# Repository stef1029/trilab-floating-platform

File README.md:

# Floating Platform Orienting System — Project Specification

A head-fixed behavioural platform for studying sensory-guided spatial orienting in mice.

> **Status:** Design specification and prototyping. This readme defines the scientific intent,
> design principles, and requirements for the system.

---

## 1. Background and Motivation

### 1.1 The problem of spatial orienting

Orienting towards environmental stimuli is a fundamental behaviour conserved across the
animal kingdom: an animal turns its eyes, head, and body to bring a salient stimulus into
its sensory and motor focus. Although subjectively effortless, orienting requires the
nervous system to solve several hard computational problems at once:

- **Coordinate-frame transformation.** Different senses encode space in incompatible
  reference frames (vision in retinotopic coordinates, hearing in head-centred coordinates,
  touch in body-centred coordinates) yet the motor system needs a single unified target.
- **Sensorimotor transformation.** A spatial estimate must be converted into a coordinated
  motor command spanning effectors with very different dynamics (fast, low-range eyes; slower,
  wider-range head; slow, widest-range body).
- **Target selection.** When multiple stimuli compete, the system must commit to a single
  target, the body cannot turn two ways at once.

### 1.2 The superior colliculus (SC)

The SC is an evolutionarily ancient midbrain hub (circuits >500 My old) that sits at the
centre of this problem. It receives topographically aligned, convergent input from
essentially every sensory modality and contains a motor map from which electrical or
optogenetic stimulation reliably evokes orienting movements toward the corresponding
location. Beyond driving movement, accumulating evidence implicates the SC in **spatial
priority / attention**: it is thought to maintain a *priority map* that integrates bottom-up
salience with top-down task relevance, gating both descending orienting commands and
ascending thalamo-cortical signals.

### 1.3 The methodological gap this system addresses

Mouse genetics (Cre-driver lines, optogenetics, optotagging, calcium imaging, two-photon,
high-density electrophysiology) make the mouse SC uniquely tractable for circuit dissection.
But existing mouse paradigms force a trade-off:

| Approach | Strength | Weakness |
|---|---|---|
| **Head-fixed** (2-photon, Neuropixels, VR) | Maximal experimental control, high trial counts, recording/manipulation access | Sacrifices the natural whole-body orienting repertoire; reporting movements are abstract (e.g. licking, wheel turns) |
| **Freely moving** (escape, prey capture, social orienting) | Full natural movement repertoire, ethological validity | Low trial counts, behavioural adaptation/disengagement, hard to standardise and track, limited tool access |

**Design thesis:** a head-fixed preparation that *preserves rotational orienting kinematics*
by mounting the animal on a low-friction, air-floated platform can recover much of the
ethological character of orienting while retaining the recording/manipulation access and
trial structure of head fixation. This is the niche the floating platform system is intended
to fill. Closely related precedents exist in the ferret sound-localisation literature
(approach-to-target paradigms) and in air-lifted platform preparations for rodents; the
novelty here is combining controlled rotational orienting with head fixation and modern
mouse circuit tools.

> **Terminology.** This document follows the *orienting* vs *localisation* distinction
> (Nodal et al., 2008). *Orienting* is the unconditioned, continuously-varying movement of
> eyes/head/body toward a stimulus. *Localisation* (approach-to-target) is the conditioned
> report of perceived location via a discrete choice. This platform is designed to capture
> the **orienting movement itself as a continuous dependent variable**, not merely the
> categorical choice.

---

## 2. Scientific Design Principles

These principles flow directly from the science above and should govern every engineering
trade-off.

1. **Preserve orienting kinematics.** The animal must be able to produce naturalistic
   rotational orienting movements. The platform's mechanics (mass, inertia, friction) must be
   matched to mouse motor capability so that orienting is *natural and low-effort*, not a
   novel motor skill the animal must laboriously acquire. **Movement accessibility is a
   first-order scientific requirement, not an engineering nicety.**

2. **Multiple spatial targets.** Move beyond binary left/right. The animal must be able to
   orient toward stimuli distributed around it, so the system can probe the full spatial map
   of the SC.

3. **Movement as the primary readout.** The dependent variable is the *trajectory* of the
   orienting movement (bearing, latency, amplitude, velocity profile), not just an endpoint.
   This demands continuous, high-resolution measurement of platform orientation.

4. **Multimodal cueing.** Support visual and auditory cues (and ideally the means to add
   somatosensory), so cue modality and coordinate frame can be dissociated — central to
   testing how heterogeneous sensory inputs are transformed into a common motor currency.

5. **Recording- and manipulation-ready from day one.** The system exists to support
   electrophysiology, optogenetics/chemogenetics, and imaging. Compatibility with these tools
   — physical access, electromagnetic compatibility, and above all **temporal
   synchronisation** — must be designed in, not retrofitted.

6. **Trial structure and throughput.** Standardised, self-paced trials with clean
   trial/inter-trial separation, at counts sufficient for statistically powerful,
   circuit-level conclusions.

7. **Respect the animal.** Welfare-conscious head fixation and handling; training timelines
   that are realistic for a cohort within a project's lifetime.

---

## 3. Requirements

### 3.1 Functional requirements (behaviour)

- **F1 — Rotational freedom.** The mouse, while head-fixed, can rotate the floating platform
  beneath it to produce orienting movements through its full natural range, with friction low
  enough that movement is effortless.
- **F2 — Constrained degrees of freedom.** Platform motion is constrained to the behaviourally
  meaningful axes (rotation, translation).
- **F3 — Multi-target cueing.** Present discrete spatial cues at ≥4 (target: 6) locations
  distributed around the animal, with unambiguous angular separation.
- **F4 — Multimodal cues.** Independently addressable **visual** (per-location LED) and
  **auditory** (per-location or spatialised speaker) cue channels; spare capacity for a third
  modality.
- **F5 — Reward delivery.** Precise, low-latency liquid reward (calibrated µL volumes) at each
  target location, with reliable consumption detection.
- **F6 — Response detection.** Detect the animal's chosen orientation/target reliably and with
  low latency (event timing to ≤1 ms), with no false positives/negatives from the sensing
  modality.
- **F7 — Self-paced trial initiation.** A clear, animal-driven readiness/initiation event that
  separates trials from inter-trial intervals and standardises starting conditions.
- **F8 — Configurable protocol.** Cue duration, cue modality, target set, reward contingency,
  timeout, and inter-trial interval all configurable per session and per training phase,
  without code surgery.

### 3.2 Measurement requirements

- **M1 — Continuous orientation tracking.** Platform angular position sampled continuously at
  high temporal resolution (target ≥100 Hz, ideally faster) and angular precision sufficient
  to reconstruct full orienting trajectories — not just endpoints.
- **M2 — Absolute reference where possible.** Orientation measurement should resolve absolute
  bearing (not only relative drift), or provide robust per-trial re-zeroing against a known
  reference event.
- **M3 — Low-light operation.** Behaviour runs under controlled, mouse-appropriate lighting
  (e.g. long-wavelength / IR illumination); the tracking method must work under these
  conditions without motion blur or illumination that interferes with the visual task.
- **M4 — Video record.** Synchronised overhead and/or side video for behavioural scoring and
  markerless pose estimation.

### 3.3 Technical / systems requirements

- **T1 — Unified timing backbone (highest priority).** A single timing authority records all
  event streams — cue onset/offset, reward, response, orientation samples, video frame
  triggers, and external equipment (ephys/laser) sync — on one clock with **≤1 ms** alignment
  across streams. *Lack of hardware-level synchronisation is the single most likely failure
  mode of a behavioural-neuroscience rig and must be solved at the architecture level.*
- **T2 — Drop detection on every stream.** Every data stream (serial messages, camera frames)
  must carry sequence IDs / frame counters so that dropped samples are detectable and
  correctable post-hoc, never silently misaligning data.
- **T3 — External-equipment sync.** Generate and/or record TTL sync with electrophysiology
  acquisition and optogenetic laser control, so neural data and behaviour share a common time
  base.
- **T4 — Electromagnetic compatibility.** Construction and grounding compatible with
  electrophysiology (shielding / Faraday behaviour; low 50 Hz pickup; no conductive paths to
  electrodes).
- **T5 — Deterministic real-time control.** Time-critical operations (reward, response
  sensing, cue timing) handled with deterministic latency; high-level trial logic and logging
  separated from real-time control.
- **T6 — Automated session lifecycle.** One-command session start that configures and launches
  all subsystems (control, acquisition, cameras) in the correct order; automated logging with
  crash recovery.
- **T7 — Standardised, analysis-ready data.** Output to a documented, standard format (e.g.
  NWB) with an accompanying pipeline from raw streams → synchronised, trial-segmented dataset
  → quality-control metrics → figures, minimising manual steps.
- **T8 — Maintainability & reproducibility.** Modular, serviceable hardware (swappable
  per-target modules); liquid-tolerant construction; documented build so additional rigs can
  be replicated by the lab.
- **T9 — Session endurance.** Sustain a full behavioural session (target: continuous operation
  for multi-hour daily use) without power, thermal, or buffer constraints forcing early
  termination.

### 3.4 Non-functional requirements

- **N1 — Welfare.** Graduated head-fixation habituation; comfortable, low-stress fixation;
  bounded session durations.
- **N2 — Trainability.** A naïve mouse should reach criterion performance within a timeframe
  practical for a 10–12 animal cohort. *(Because mechanical accessibility (F1) directly
  governs trainability, the platform's inertia/friction budget should be validated against
  mouse motor output early.)*
- **N3 — Cost & scalability.** Favour designs that allow multiple rigs to run in parallel on
  shared infrastructure without duplicating the most expensive components.

---

## 4. Proposed System Description

A concrete architecture that satisfies the requirements above. Subsystems are described by
*function and constraints*; exact components are deliberately left open where the science does
not yet dictate them.

### 4.1 Mechanical core — the floating platform

- A lightweight, rigid platform (e.g. machined low-density foam) suspended on a **cushion of
  air** above a perforated, regulated air table, giving near-frictionless motion.
- Air supply regulated to lift the loaded platform (platform + onboard electronics) at a
  stable hover height with negligible residual friction.
- **Motion constrained** to the behaviourally relevant axes — primarily rotation (and
  optionally controlled fore/aft translation) — using physical guides, while blocking
  lateral/vertical excursions.
- **Inertia budget:** the rotational moment of inertia of the loaded platform must be small
  relative to the torque a mouse can comfortably generate. This is the central mechanical
  constraint and should be minimised (light platform, minimal onboard mass, balanced about the
  rotation axis) and validated empirically against mouse motor capability before committing.
- A low surrounding wall prevents falls without restricting movement and provides a mounting
  surface for cue/reward modules and/or tracking references.

### 4.2 Head-fixation assembly

- Standard, welfare-conscious head-bar fixation (off-the-shelf optomechanics) positioning the
  animal centrally over the platform's rotation axis, leaving the body free to drive platform
  rotation.
- Fixation height and posture chosen so that orienting is produced by natural weight-shift /
  stepping, not an artificial motor strategy.

### 4.3 Target / cue / reward modules

- A ring of **modular, independently serviceable target stations** at fixed angular intervals
  (target: 6 at 60°, minimum 4 at 90°).
- Each station integrates: a **visual cue** (high-brightness LED), an **auditory cue**
  (speaker), a **liquid reward** spout (solenoid/pinch-valve, gravity- or pump-fed, calibrated
  volume), and a **response/consumption sensor** (e.g. IR beam-break — preferred over
  capacitive sensing for reliability).
- Modularity allows a faulty station to be swapped without disturbing the rig and supports
  rapid prototyping of new configurations.

### 4.4 Orientation tracking

Continuous platform-orientation measurement is mandatory (M1–M3). The architecture should
support — and ideally fuse — complementary methods, chosen for robustness under low-light
operation:

- An **inertial measurement unit (IMU)** mounted on the platform for high-rate relative
  orientation, re-zeroed each trial against a known reference event (giving high within-trial
  accuracy).
- And/or an **absolute optical reference** (e.g. fiducial markers read by a camera, or an
  optical/magnetic angular encoder on the rotation axis) for absolute bearing and drift
  correction — noting that any camera-based method must tolerate the IR/low-light regime and
  platform motion without blur.
- **Markerless pose estimation** (e.g. DeepLabCut) on synchronised video as an independent
  cross-check and for body/limb kinematics.

### 4.5 Control and acquisition architecture

The defining architectural commitment: **separate real-time control from timing/logging.**

- **Real-time controller** (microcontroller): owns deterministic, time-critical hardware
  control — cue timing, reward actuation, response sensing — and nothing else. Prefer a
  microcontroller with **native USB** (low, deterministic serial latency) over legacy
  serial-to-USB bridges.
- **Independent acquisition / timing backbone (DAQ):** a dedicated device that does nothing
  but sample *all* digital/analogue lines (cue states, sensor states, reward signals) plus
  external sync (camera frame TTLs, ephys clock, laser control) at high rate (target ≥1 kHz,
  ideally ≥10 kHz) onto **one clock**. Every message carries a sequence ID (T2).
- **Host computer:** runs high-level trial logic / state machine, configuration, multi-rig
  orchestration, real-time performance metrics, and all file writing (offloading I/O from
  embedded devices). Launches the whole session with one command (T6).
- **Cameras:** programmatically controlled (not via a GUI), emitting a TTL per frame into the
  DAQ and saving hardware frame IDs, so dropped frames are detectable and video aligns to the
  behavioural timeline to the frame.

This separation is what delivers T1–T3: a single timestamped record into which neural,
video, and behavioural events all map without clock drift.

### 4.6 Software, data, and analysis pipeline

- **Configurable protocol engine** encoding training phases and trial parameters via
  configuration, not code edits (F8).
- **Standardised output** (NWB or equivalent) bundling synchronised event streams, orientation
  traces, video references, and trial metadata, with crash-recovery/backup.
- **Automated post-processing**: parse DAQ logs → reconstruct trials → align video via frame
  IDs → run pose estimation → emit a trial-segmented dataset plus QC metrics, with minimal
  manual intervention.
- **Cohort/session data model** giving programmatic access (query by animal, date, completion
  status) so analyses run over whole cohorts in little code.

### 4.7 Behavioural protocol (intended)

1. **Initiation.** The animal produces a defined, self-paced readiness event that standardises
   the starting orientation and separates trials from inter-trial intervals (F7). The
   initiation requirement must be designed to genuinely standardise starting conditions
   (minimising preparatory movement before cue onset).
2. **Cue.** One target is cued (visual and/or auditory), with configurable duration.
3. **Orienting response.** The animal rotates the platform to bring the cued target into
   reach; the full trajectory is recorded.
4. **Outcome.** Correct orientation → immediate calibrated reward. Incorrect → brief timeout,
   no reward.
5. **Reset.** Return to initiation for the next self-paced trial.

---

## 5. Key Open Design Questions / Risks

Flagged up front because they drive the riskiest decisions:

- **Mechanical accessibility vs. control (F1/N2).** Can the inertia/friction budget be made
  low enough that a head-fixed mouse produces natural orienting rotations *and* learns the task
  in a cohort-feasible timeframe? This is the make-or-break biological-mechanical question and
  should be de-risked first with simple motor-capability tests.
- **Tracking under low light (M1–M3).** Reconciling absolute, blur-free, high-rate orientation
  measurement with the dim/IR lighting the visual task requires. IMU + absolute-encoder fusion
  is the conservative hedge.
- **Initiation standardisation (F7).** Defining an initiation behaviour that truly fixes
  starting orientation without permitting covert preparatory movement.
- **Synchronisation throughput (T1).** Achieving the target sample/frame rates without
  message loss; choice of controller and DAQ should leave headroom above the minimum.

---

## 6. Key References

Foundational citations that justify the design intent.

**Superior colliculus, orienting, and spatial priority**
- May, P. J. (2006). The mammalian superior colliculus: laminar structure and connections.
  *Prog. Brain Res.* 151. — SC anatomy and laminar organisation.
- Sparks, D. L. & Mays, L. E. (1990). Signal transformations required for the generation of
  saccadic eye movements. *Annu. Rev. Neurosci.* 13. — SC sensorimotor transformation.
- Fecteau, J. H. & Munoz, D. P. (2006). Salience, relevance, and firing: a priority map for
  target selection. *Trends Cogn. Sci.* 10. — priority-map concept.
- Krauzlis, R. J., Lovejoy, L. P. & Zénon, A. (2013). Superior colliculus and visual spatial
  attention. *Annu. Rev. Neurosci.* 36. — SC role in attention beyond movement.
- Knudsen, E. I. (2018). Neural circuits that mediate selective attention: a comparative
  perspective. *Trends Neurosci.* 41. — gating and selective attention.
- de Malmazet, D. & Tripodi, M. (2023). Collicular circuits supporting the perceptual, motor
  and cognitive demands of ethological environments. *Curr. Opin. Neurobiol.* 82.
- Masullo, L. et al. (2019). Genetically defined functional modules for spatial orienting in
  the mouse superior colliculus. *Curr. Biol.* 29. — Pitx2+ SC output neurons; target
  population for manipulation.

**Behavioural paradigms and precedents**
- Parsons, C. H., Lanyon, R. G., Schnupp, J. W. H. & King, A. J. (1999). *J. Neurophysiol.* 82.
  — ferret sound-localisation / approach-to-target precedent.
- Nodal, F. R. et al. (2008). Sound localisation behaviour in ferrets: acoustic orientation vs
  approach-to-target. *Neuroscience* 154. — the orienting vs localisation distinction.
- Robbins, T. W. (2002). The 5-choice serial reaction time task. *Psychopharmacology* 163. —
  multi-choice spatial reporting paradigm.
- Guo, Z. V. et al. (2014). Procedures for behavioral experiments in head-fixed mice. *PLoS
  ONE* 9. — head-fixed behavioural standards.
- Kislin, M. et al. (2014). Flat-floored air-lifted platform: combining behaviour with
  microscopy/electrophysiology on awake freely moving rodents. *JoVE*. — air-lifted platform
  precedent.
- Angelaki, D. et al. (2025). A brain-wide map of neural activity during complex behaviour.
  *Nature* 645. — mice performing complex standardised tasks.

**Tools and infrastructure**
- Denman, D. J. et al. (2017). Chromatic pathways in the mouse dLGN. *J. Neurosci.* 37. —
  basis for long-wavelength lighting choices for mouse vision.
- Mathis, A. et al. (2018). DeepLabCut: markerless pose estimation. *Nat. Neurosci.* 21.
- Rübel, O. et al. (2022). The Neurodata Without Borders ecosystem. *eLife* 11. — standardised
  data format.

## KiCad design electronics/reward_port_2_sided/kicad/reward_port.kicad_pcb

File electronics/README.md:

# Electronics

KiCad projects, schematics, PCB layouts, BOMs, and fabrication outputs.

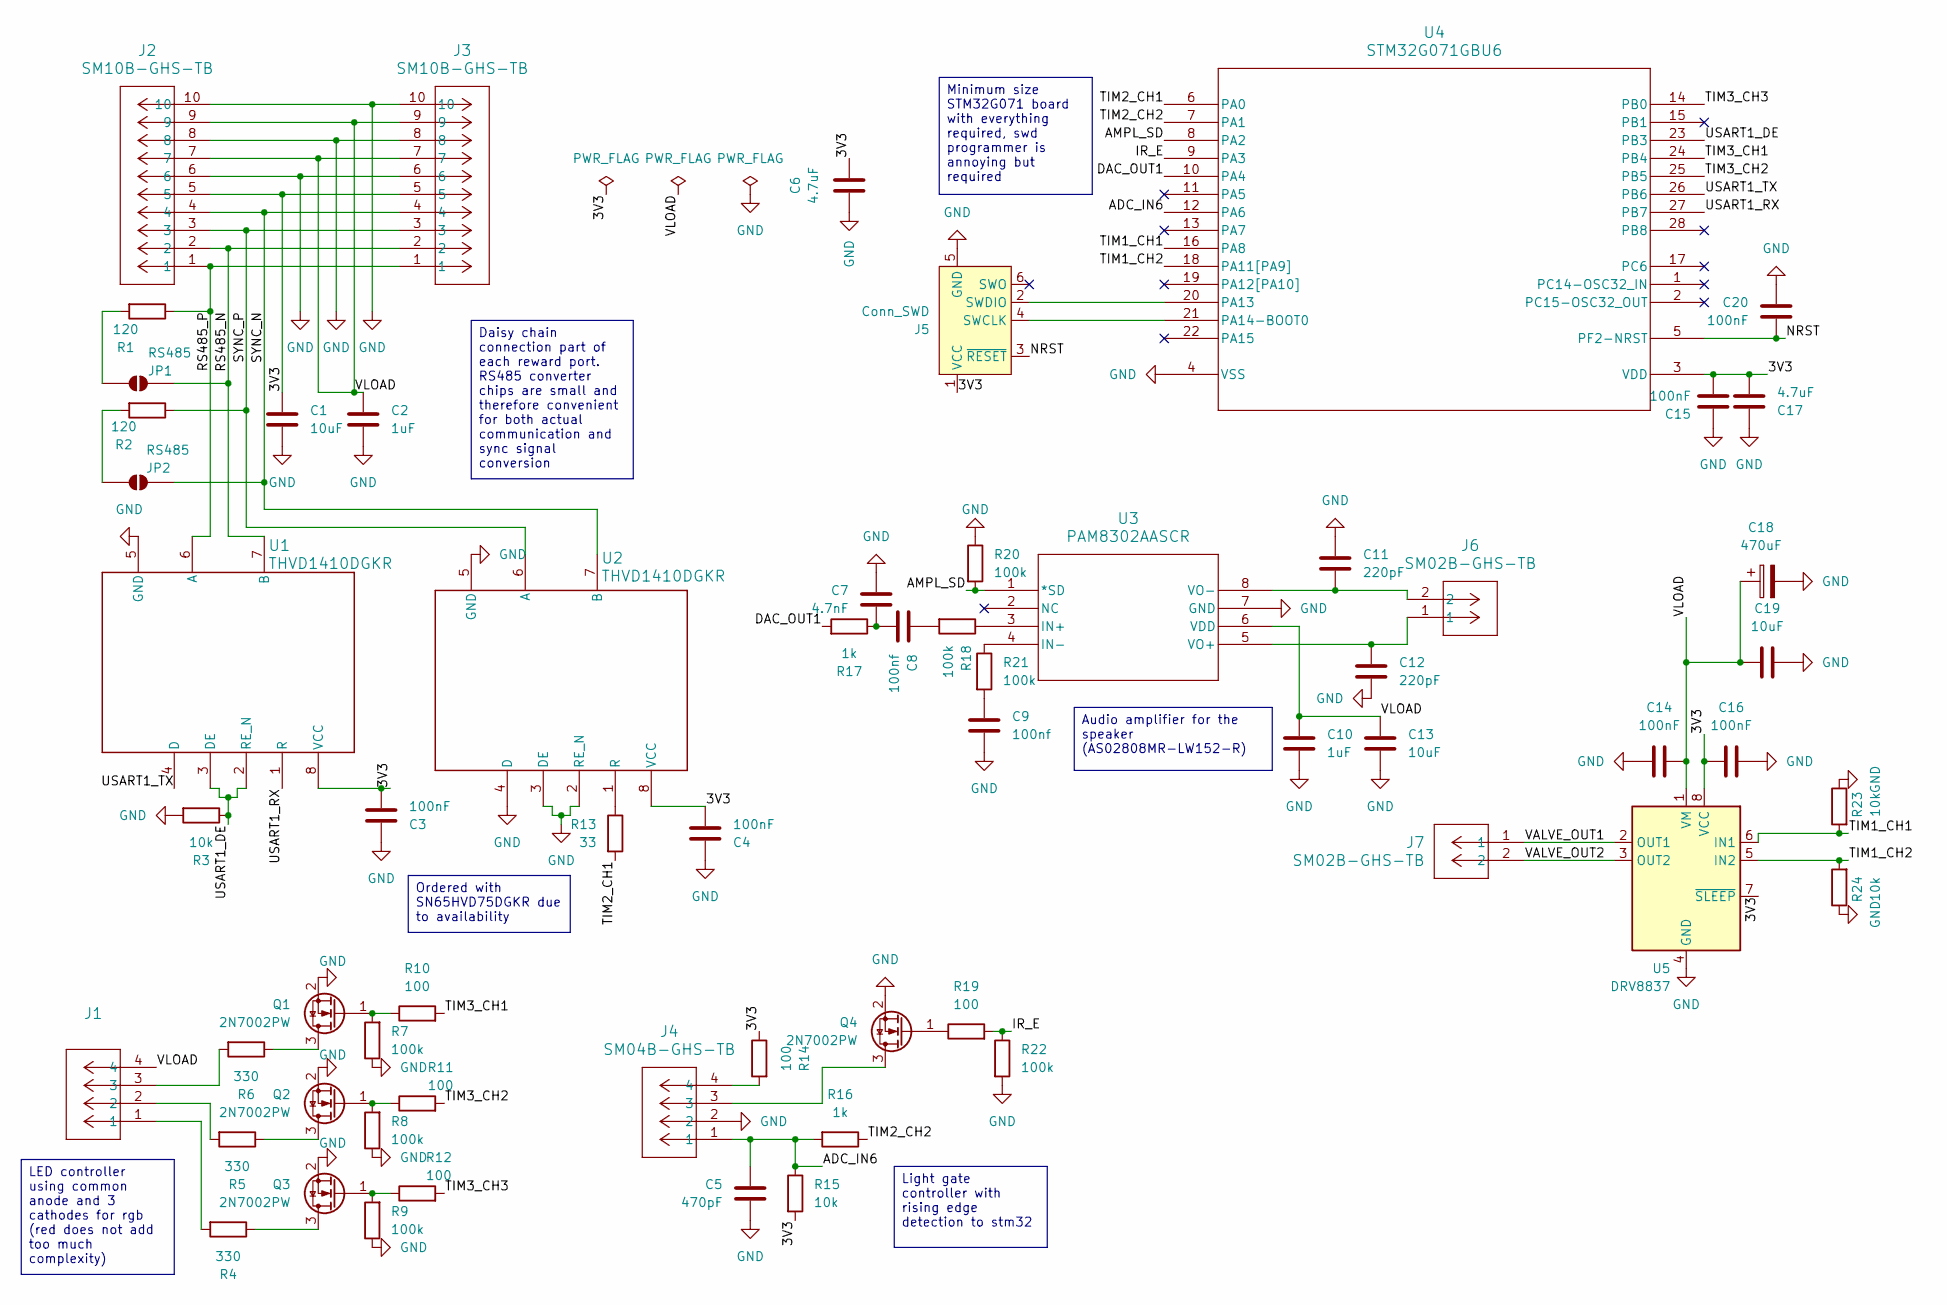
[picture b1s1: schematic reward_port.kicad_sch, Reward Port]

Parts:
C1, C19: 10uF; C_0603_1608Metric
C2, C10: 1uF; C_0402_1005Metric
C3, C4, C14, C15, C16, C20: 100nF; C_0402_1005Metric
C5: 470pF; C_0402_1005Metric
C6, C17: 4.7uF; C_0603_1608Metric
C7: 4.7nF; C_0402_1005Metric
C8, C9: 100nf; C_0402_1005Metric
C11, C12: 220pF; C_0402_1005Metric
C13: 10uF; C_0805_2012Metric
C18: 470uF; CP_EIA-7343-43_Kemet-X
J1, J4: SM04B-GHS-TB; JST_GH_SM04B-GHS-TB_1x04-1MP_P1.25mm_Horizontal
J2, J3: SM10B-GHS-TB; JST_PH_S10B-PH-SM4-TB_1x10-1MP_P2.00mm_Horizontal
J5: Conn_SWD; Tag-Connect_TC2030-IDC-NL_2x03_P1.27mm_Vertical
J6, J7: SM02B-GHS-TB; JST_GH_SM02B-GHS-TB_1x02-1MP_P1.25mm_Horizontal
JP1, JP2: RS485; SolderJumper-2_P1.3mm_Open_RoundedPad1.0x1.5mm
Q1, Q2, Q3, Q4: 2N7002PW; SOT-323_SC-70
R1, R2: 120; R_0603_1608Metric
R3, R15, R23, R24: 10k; R_0402_1005Metric
R4, R5, R6: 330; R_0402_1005Metric
R7, R8, R9, R18, R20, R21, R22: 100k; R_0402_1005Metric
R10, R11, R12, R19: 100; R_0402_1005Metric
R13: 33; R_0402_1005Metric
R14: 100; R_0603_1608Metric
R16, R17: 1k; R_0402_1005Metric
U1, U2: THVD1410DGKR; VSSOP-8_3x3mm_P0.65mm
U3: PAM8302AASCR; PAM8302AASCR_DIO
U4: STM32G071GBU6; QFN-28_4x4mm_P0.5mm
U5: DRV8837; WSON-8-1EP_2x2mm_P0.5mm_EP0.9x1.6mm

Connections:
/3V3: C1.1, C3.1, C4.1, C6.1, C15.2, C16.1, C17.1, J2.5, J3.5, J5.1 (VCC), R14.1, R15.2, U1.8 (VCC), U2.8 (VCC), U4.3 (VDD), U5.7 (~SLEEP), U5.8 (VCC)
/ADC_IN6: C5.2, J4.1, R15.1, R16.2, U4.12 (PA6)
/AMPL_SD: R20.2, U3.1 (*SD), U4.8 (PA2)
/DAC_OUT1: R17.2, U4.10 (PA4)
/IR_E: R19.2, R22.1, U4.9 (PA3)
/NRST: C20.1, J5.3 (~RESET), U4.5 (PF2-NRST)
/RS485_N: J2.2, J3.2, JP1.2 (B), U1.7 (B)
/RS485_P: J2.1, J3.1, R1.1, U1.6 (A)
/SYNC_N: J2.4, J3.4, JP2.2 (B), U2.7 (B)
/SYNC_P: J2.3, J3.3, R2.1, U2.6 (A)
/TIM1_CH1: R23.2, U4.16 (PA8), U5.6 (IN1)
/TIM1_CH2: R24.2, U4.18 (PA11[PA9]), U5.5 (IN2)
/TIM2_CH1: R13.2, U4.6 (PA0)
/TIM2_CH2: R16.1, U4.7 (PA1)
/TIM3_CH1: R10.2, U4.24 (PB4)
/TIM3_CH2: R11.2, U4.25 (PB5)
/TIM3_CH3: R12.2, U4.14 (PB0)
/USART1_DE: R3.1, U1.2 (RE_N), U1.3 (DE), U4.23 (PB3)
/USART1_RX: U1.1 (R), U4.27 (PB7)
/USART1_TX: U1.4 (D), U4.26 (PB6)
/VALVE_OUT1: J7.1, U5.2 (OUT1)
/VALVE_OUT2: J7.2, U5.3 (OUT2)
/VLOAD: C2.1, C10.1, C13.1, C14.1, C18.1, C19.1, J1.4, J2.7, J2.9, J3.7, J3.9, U3.6 (VDD), U5.1 (VM)
GND: C1.2, C2.2, C3.2, C4.2, C5.1, C6.2, C7.1, C9.2, C10.2, C11.1, C12.1, C13.2, C14.2, C15.1, C16.2, C17.2, C18.2, C19.2, C20.2, J2.6, J2.8, J2.10, J3.6, J3.8, J3.10, J4.2, J5.5 (GND), Q1.2 (S), Q2.2 (S), Q3.2 (S), Q4.2 (S), R3.2, R7.1, R8.1, R9.1, R20.1, R22.2, R23.1, R24.1, U1.5 (GND), U2.2 (RE_N), U2.3 (DE), U2.4 (D), U2.5 (GND), U3.7 (GND), U4.4 (VSS), U5.4 (GND), U5.9 (GND)
unnamed: C7.2, C8.2, R17.1
unnamed: C8.1, R18.2
unnamed: C9.1, R21.2
unnamed: J1.1, R4.2
unnamed: J1.2, R5.2
unnamed: J1.3, R6.2
unnamed: J4.4, R14.2
unnamed: J5.4 (SWCLK), U4.21 (PA14-BOOT0)
unnamed: J5.2 (SWDIO), U4.20 (PA13)
unnamed: JP1.1 (A), R1.2
unnamed: JP2.1 (A), R2.2
unnamed: Q1.3 (D), R6.1
unnamed: Q1.1 (G), R7.2, R10.1
unnamed: Q2.3 (D), R5.1
unnamed: Q2.1 (G), R8.2, R11.1
unnamed: Q3.3 (D), R4.1
unnamed: Q3.1 (G), R9.2, R12.1
unnamed: J4.3, Q4.3 (D)
unnamed: Q4.1 (G), R19.1
unnamed: R13.1, U2.1 (R)
unnamed: R18.1, U3.3 (IN+)
unnamed: R21.1, U3.4 (IN-)
unnamed: C12.2, J6.1, U3.5 (VO+)
unnamed: C11.2, J6.2, U3.8 (VO-)

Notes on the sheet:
Audio amplifier for the speaker (AS02808MR-LW152-R)
Light gate controller with rising edge detection to stm32
Daisy chain connection part of each reward port. RS485 converter chips are small and therefore convenient for both actual communication and sync signal conversion
Minimum size STM32G071 board with everything required, swd programmer is annoying but required
Ordered with SN65HVD75DGKR due to availability
LED controller using common anode and 3 cathodes for rgb (red does not add too much complexity)

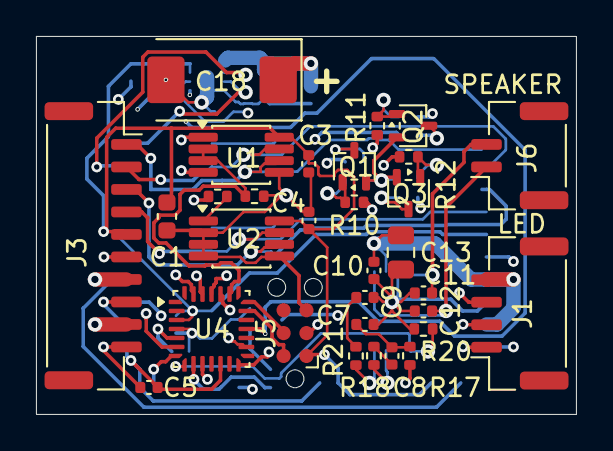
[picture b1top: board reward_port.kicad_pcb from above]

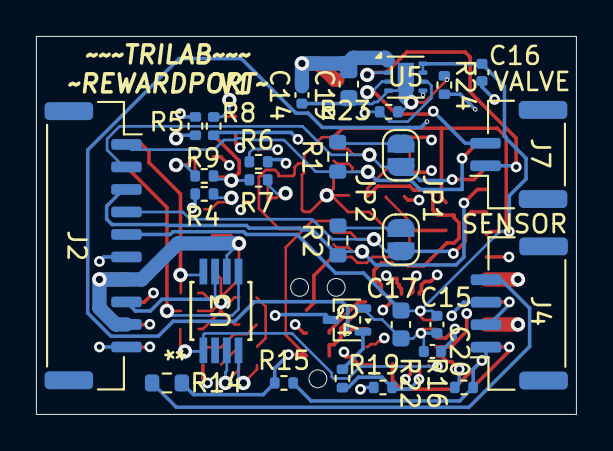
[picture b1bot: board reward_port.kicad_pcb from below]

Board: 4 copper layers, 30.0 x 21.0 mm, 60 parts (29 on the bottom side), 48 nets.

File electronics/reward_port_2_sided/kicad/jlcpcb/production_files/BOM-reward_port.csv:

Comment,Designator,Footprint,LCSC,Quantity
100,R14,R_0603_1608Metric,C22775,1
100,"R10,R11,R12,R19",R_0402_1005Metric,C25076,4
100k,"R18,R20,R21,R22,R7,R8,R9",R_0402_1005Metric,C25741,7
100nF,"C14,C15,C16,C20,C3,C4",C_0402_1005Metric,C307331,6
100nf,"C8,C9",C_0402_1005Metric,C307331,2
10k,"R15,R23,R3",R_0402_1005Metric,C25744,3
10uF,C13,C_0805_2012Metric,C440198,1
10uF,"C1,C19",C_0603_1608Metric,C96446,2
120,"R1,R2",R_0603_1608Metric,C14709,2
1k,"R16,R17",R_0402_1005Metric,C11702,2
1uF,C10,C_0402_1005Metric,C52923,1
220pF,"C11,C12",C_0402_1005Metric,C1530,2
2N7002PW,"Q1,Q2,Q3,Q4",SOT-323_SC-70,C5224236,4
33,R13,R_0402_1005Metric,C25105,1
330,"R4,R5,R6",R_0402_1005Metric,C25104,3
4.7nF,C7,C_0402_1005Metric,C1538,1
4.7uF,C17,C_0603_1608Metric,C19666,1
470pF,C5,C_0402_1005Metric,C1537,1
470uF,C18,CP_EIA-7343-43_Kemet-X,C506631,1
DRV8837,U5,WSON-8-1EP_2x2mm_P0.5mm_EP0.9x1.6mm,C39159,1
PAM8302AASCR,U3,PAM8302AASCR_DIO,C113367,1
SM02B-GHS-TB,"J6,J7",JST_GH_SM02B-GHS-TB_1x02-1MP_P1.25mm_Horizontal,C189893,2
SM04B-GHS-TB,"J1,J4",JST_GH_SM04B-GHS-TB_1x04-1MP_P1.25mm_Horizontal,C51940118,2
SM10B-GHS-TB,"J2,J3",JST_GH_SM10B-GHS-TB_1x10-1MP_P1.25mm_Horizontal,C2683602,2
STM32G071GBU6,U4,QFN-28_4x4mm_P0.5mm,C529347,1
THVD1410DGKR,"U1,U2",VSSOP-8_3x3mm_P0.65mm,C179693,2

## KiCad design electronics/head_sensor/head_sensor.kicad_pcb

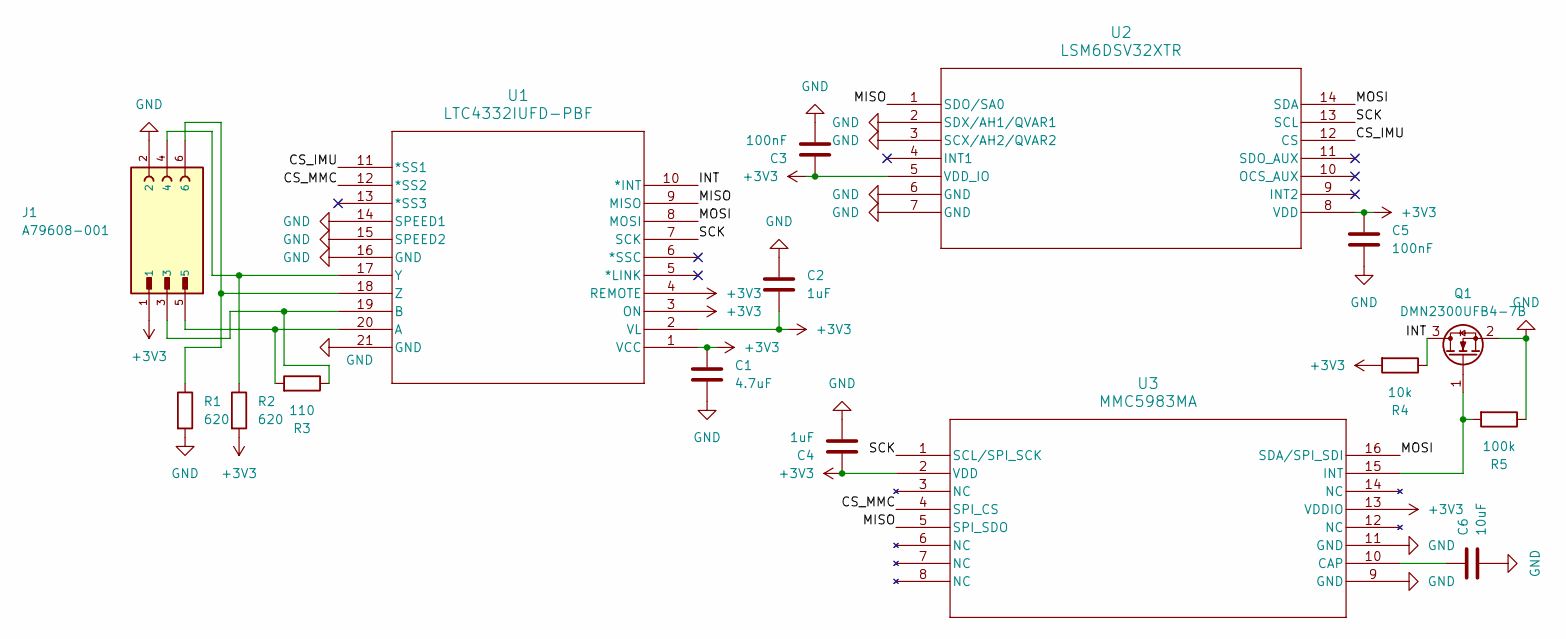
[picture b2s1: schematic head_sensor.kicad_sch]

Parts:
C1: 4.7uF; C_0603_1608Metric
C2, C4: 1uF; C_0402_1005Metric
C3, C5: 100nF; C_0402_1005Metric
C6: 10uF; C_0603_1608Metric
J1: A79608-001; OMNETICS_A79607-001; PARTREV D
Q1: DMN2300UFB4-7B; Diodes_DFN1006-3
R1, R2: 620; R_0402_1005Metric
R3: 110; R_0402_1005Metric
R4: 10k; R_0402_1005Metric
R5: 100k; R_0402_1005Metric
U1: LTC4332IUFD-PBF; UFD_05-08-1711_ADI
U2: LSM6DSV32XTR; LGA-14_3x2.5mm_P0.5mm_LayoutBorder3x4y
U3: MMC5983MA; LGA-16_3x3mm_P0.5mm

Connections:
+3V3: C1.1, C2.2, C3.1, C4.1, C5.1, J1.1, R2.2, R4.2, U1.1 (VCC), U1.2 (VL), U1.3 (ON), U1.4 (REMOTE), U2.5 (VDD_IO), U2.8 (VDD), U3.2 (VDD), U3.13 (VDDIO)
/CS_IMU: U1.11 (*SS1), U2.12 (CS)
/CS_MMC: U1.12 (*SS2), U3.4 (SPI_CS)
/INT: Q1.3 (D), R4.1, U1.10 (*INT)
/MISO: U1.9 (MISO), U2.1 (SDO/SA0), U3.5 (SPI_SDO)
/MOSI: U1.8 (MOSI), U2.14 (SDA), U3.16 (SDA/SPI_SDI)
/SCK: U1.7 (SCK), U2.13 (SCL), U3.1 (SCL/SPI_SCK)
GND: C1.2, C2.1, C3.2, C4.2, C5.2, C6.2, J1.2, Q1.2 (S), R1.2, R5.1, U1.14 (SPEED1), U1.15 (SPEED2), U1.16 (GND), U1.21 (GND), U2.2 (SDX/AH1/QVAR1), U2.3 (SCX/AH2/QVAR2), U2.6 (GND), U2.7 (GND), U3.9 (GND), U3.11 (GND)
unnamed: Q1.1 (G), R5.2, U3.15 (INT)
unnamed: J1.5, R3.2, U1.20 (A)
unnamed: J1.3, R3.1, U1.19 (B)
unnamed: J1.4, R2.1, U1.17 (Y)
unnamed: J1.6, R1.1, U1.18 (Z)
unnamed: C6.1, U3.10 (CAP)

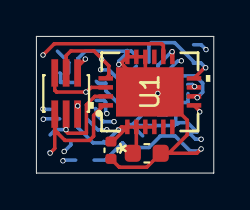
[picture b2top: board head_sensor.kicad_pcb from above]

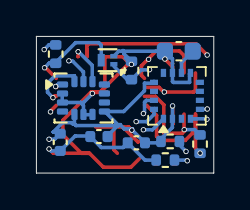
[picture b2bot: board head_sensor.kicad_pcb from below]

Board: 4 copper layers, 9.8 x 7.6 mm, 16 parts (12 on the bottom side), 14 nets.

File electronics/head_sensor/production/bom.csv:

Designator,Footprint,Quantity,Value,LCSC Part #
C1,0603,1,4.7uF,
"C2, C4",0402,2,1uF,
"C3, C5",0402,2,100nF,
C6,0603,1,10uF,
J1,OMNETICS_A79607-001,1,A79608-001,
Q1,Diodes_DFN1006-3,1,DMN2300UFB4-7B,
"R1, R2",0402,2,620,
R3,0402,1,110,
R4,0402,1,10k,
R5,0402,1,100k,
U1,UFD_05-08-1711_ADI,1,LTC4332IUFD-PBF,
U2,LGA-14_3x2.5mm_P0.5mm_LayoutBorder3x4y,1,LSM6DSV32XTR,
U3,LGA-16_3x3mm_P0.5mm,1,MMC5983MA,

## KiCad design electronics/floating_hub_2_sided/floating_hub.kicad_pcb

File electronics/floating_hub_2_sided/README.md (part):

# Korora Hub

Central nRF52840-based hub board for the behavioural rig. Korora provides:

- RS-485 master communication to peripheral boards
- Differential SYNC distribution to peripheral boards
- System time authority and synchronization
- 9-DoF motion/orientation sensing
- LiPo battery charging and power-path management
- Battery / power telemetry to the nRF52840
- 3V3 and VLOAD distribution over the peripheral harness
- USB/SWD-style development and debug access as appropriate for the final PCB

The current controller module is the BMD-340-A-R, based on the nRF52840.

The current power-management assumption is an nPM1300-class Nordic PMIC. Exact PMIC variant, battery connector, thermistor arrangement, charge current, and rail configuration must be finalized against the selected battery before schematic release.

## System architecture

Korora is the system master.

The hub:

- owns the system timebase
- initiates RS-485 transactions
- emits the differential SYNC signal
- gathers peripheral event timestamps
- translates peripheral-local timestamps into hub/system time
- acquires the local IMU and magnetometer
- runs or hosts the 9-DoF orientation-fusion algorithm
- monitors battery and power state
- distributes 3V3, VLOAD, and ground to the peripheral chain

Initial high-level architecture:

```text
                         +----------------------+
5V BENCH INPUT --------->|                      |
                         |       nPM PMIC       |
LiPo BATTERY ----------->| charger / fuel gauge|
                         | power-path / bucks   |
                         +----+-------------+---+
                              |             |
                             3V3           VSYS
                              |             |
                              |             +---------- VLOAD
                              |                         |
                              +-------------------------+--> JST-GH
                              |
                    +---------+---------+
                    |    BMD-340-A-R    |
                    |      nRF52840     |
                    +----+----+----+----+
                         |    |    |
                      UART   GPIO  I2C/SPI
                         |    |    |
                         |    |    +----> IMU
                         |    |    +----> magnetometer
                         |    |    +----> PMIC telemetry
                         |    |
                         |    +---------> SN65HVD75 #2
                         |                  SYNC_P/N
                         |
                         +-------------> SN65HVD75 #1
                                            RS485_P/N
```

## Relationship to peripheral boards

Korora is designed to connect directly to peripheral boards using the common 10-pin JST-GH bus.

Korora is the RS-485 bus master and the source of the differential SYNC pulse. Peripheral boards are expected to:

- listen for hub commands
- transmit only when addressed
- capture SYNC locally in hardware
- report captured timestamps and local events back to Korora

The initial Reward Port design assumes a 500000 baud, 8-N-1, half-duplex RS-485 link and an initially 4 Hz SYNC pulse.

These values are initial protocol parameters rather than permanent electrical limitations.

## Power inputs

Korora has two power sources:

1. LiPo battery
2. External 5 V bench / development supply

The PMIC provides charging and power-path control between them.

### Battery input

The earlier system requirement described the battery as approximately 4.3 V.

Do not set the PMIC charge termination voltage from that description alone. The final battery datasheet controls:

- maximum charge voltage
- charge current
- temperature limits
- NTC requirements
- minimum discharge voltage
- protection requirements

### Bench power input

Provide a 2-pin header for development power:

| Pin | Signal    |
| --: | --------- |
|   1 | +5V_BENCH |
|   2 | GND       |

The bench input feeds the PMIC input rather than directly feeding the battery rail.

Intended behaviour:

```text
5 V bench present
        |
        v
      PMIC
      /  \
     /    +----> system load
    |
    +---------> battery charging
```

The bench supply must be current limited during initial bring-up.

## Power rails

Korora distributes two positive rails to the peripheral connector.

### 3V3

3V3 is the regulated digital rail.

Expected loads include:

- BMD-340-A-R
- RS-485 transceivers
- local sensors
- PMIC digital interface as required
- peripheral-board 3V3 loads through the JST-GH chain

The total required 3V3 current is TBD.

Before finalizing the PMIC configuration, calculate:

```text
hub local 3V3 load
+
maximum number of peripheral boards
x
maximum peripheral 3V3 load
=
required regulated 3V3 current
```

If this exceeds the useful continuous current available from the selected PMIC regulator configuration, Korora requires an external 3V3 regulator or a revised power architecture.

### VLOAD

VLOAD is currently defined as the PMIC system / VSYS rail.

VLOAD is not assumed to be a precision regulated 5 V rail.

Conceptually:

```text
battery operation:
battery -> PMIC power path -> VSYS -> VLOAD

bench operation:
5 V input -> PMIC power path -> VSYS -> VLOAD
```

Therefore VLOAD may vary with power-source state and battery condition.

Peripheral loads must be designed for the specified VLOAD operating range.

The final VLOAD voltage range and current limit must be documented after the PMIC and battery design are finalized.

## PMIC interface

Korora should provide a digital control / telemetry link between the PMIC and the nRF52840.

Current intended interface:

```text
BMD-340 SDA <------> PMIC SDA
BMD-340 SCL -------> PMIC SCL
PMIC IRQ ----------> BMD-340 GPIO
```

The firmware should be able to query and log, where supported by the selected PMIC configuration:

- battery voltage
- battery current
- input-source state
- charging state
- state of charge
- battery health / aging information
- PMIC fault state
- regulator state
- power-loss or low-battery warnings

Exact registers and reported metrics depend on the final PMIC implementation.

## Main controller

Controller module:

```text
BMD-340-A-R
nRF52840
```

Korora uses the nRF52840 for:

- system timing
- RS-485 protocol
- SYNC generation
- peripheral discovery and polling
- event collection
- sensor acquisition
- sensor fusion
- battery telemetry
- BLE / radio functionality if required
- diagnostics
- firmware update / development functions

## BMD-340 pin assignment

Physical BMD-340 pin numbers are not yet frozen.

Reserve logical functions for:

| Function             | Peripheral / type          | Notes                      |
| -------------------- | -------------------------- | -------------------------- |
| RS-485 transmit      | UARTE TX                   | Main peripheral bus        |
| RS-485 receive       | UARTE RX                   | Main peripheral bus        |
| RS-485 driver enable | GPIO or UARTE DE strategy  | Must default bus-safe      |
| SYNC output          | GPIO / timer-driven output | Feeds second RS-485 driver |
| PMIC SDA             | TWIM / I2C                 | Shared bus possible        |
| PMIC SCL             | TWIM / I2C                 | Shared bus possible        |
| PMIC interrupt       | GPIO input                 | Optional but recommended   |
| IMU bus              | SPI or I2C                 | Final choice TBD           |
| IMU interrupt 1      | GPIO input                 | Data-ready / FIFO event    |
| IMU interrupt 2      | GPIO input                 | Optional                   |
| Magnetometer bus     | I2C or SPI                 | Final choice TBD           |
| Magnetometer DRDY    | GPIO input                 | Optional but recommended   |
| SWDIO                | SWD                        | Debug                      |
| SWDCLK               | SWD                        | Debug                      |
| RESET                | reset                      | Debug / recovery           |

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
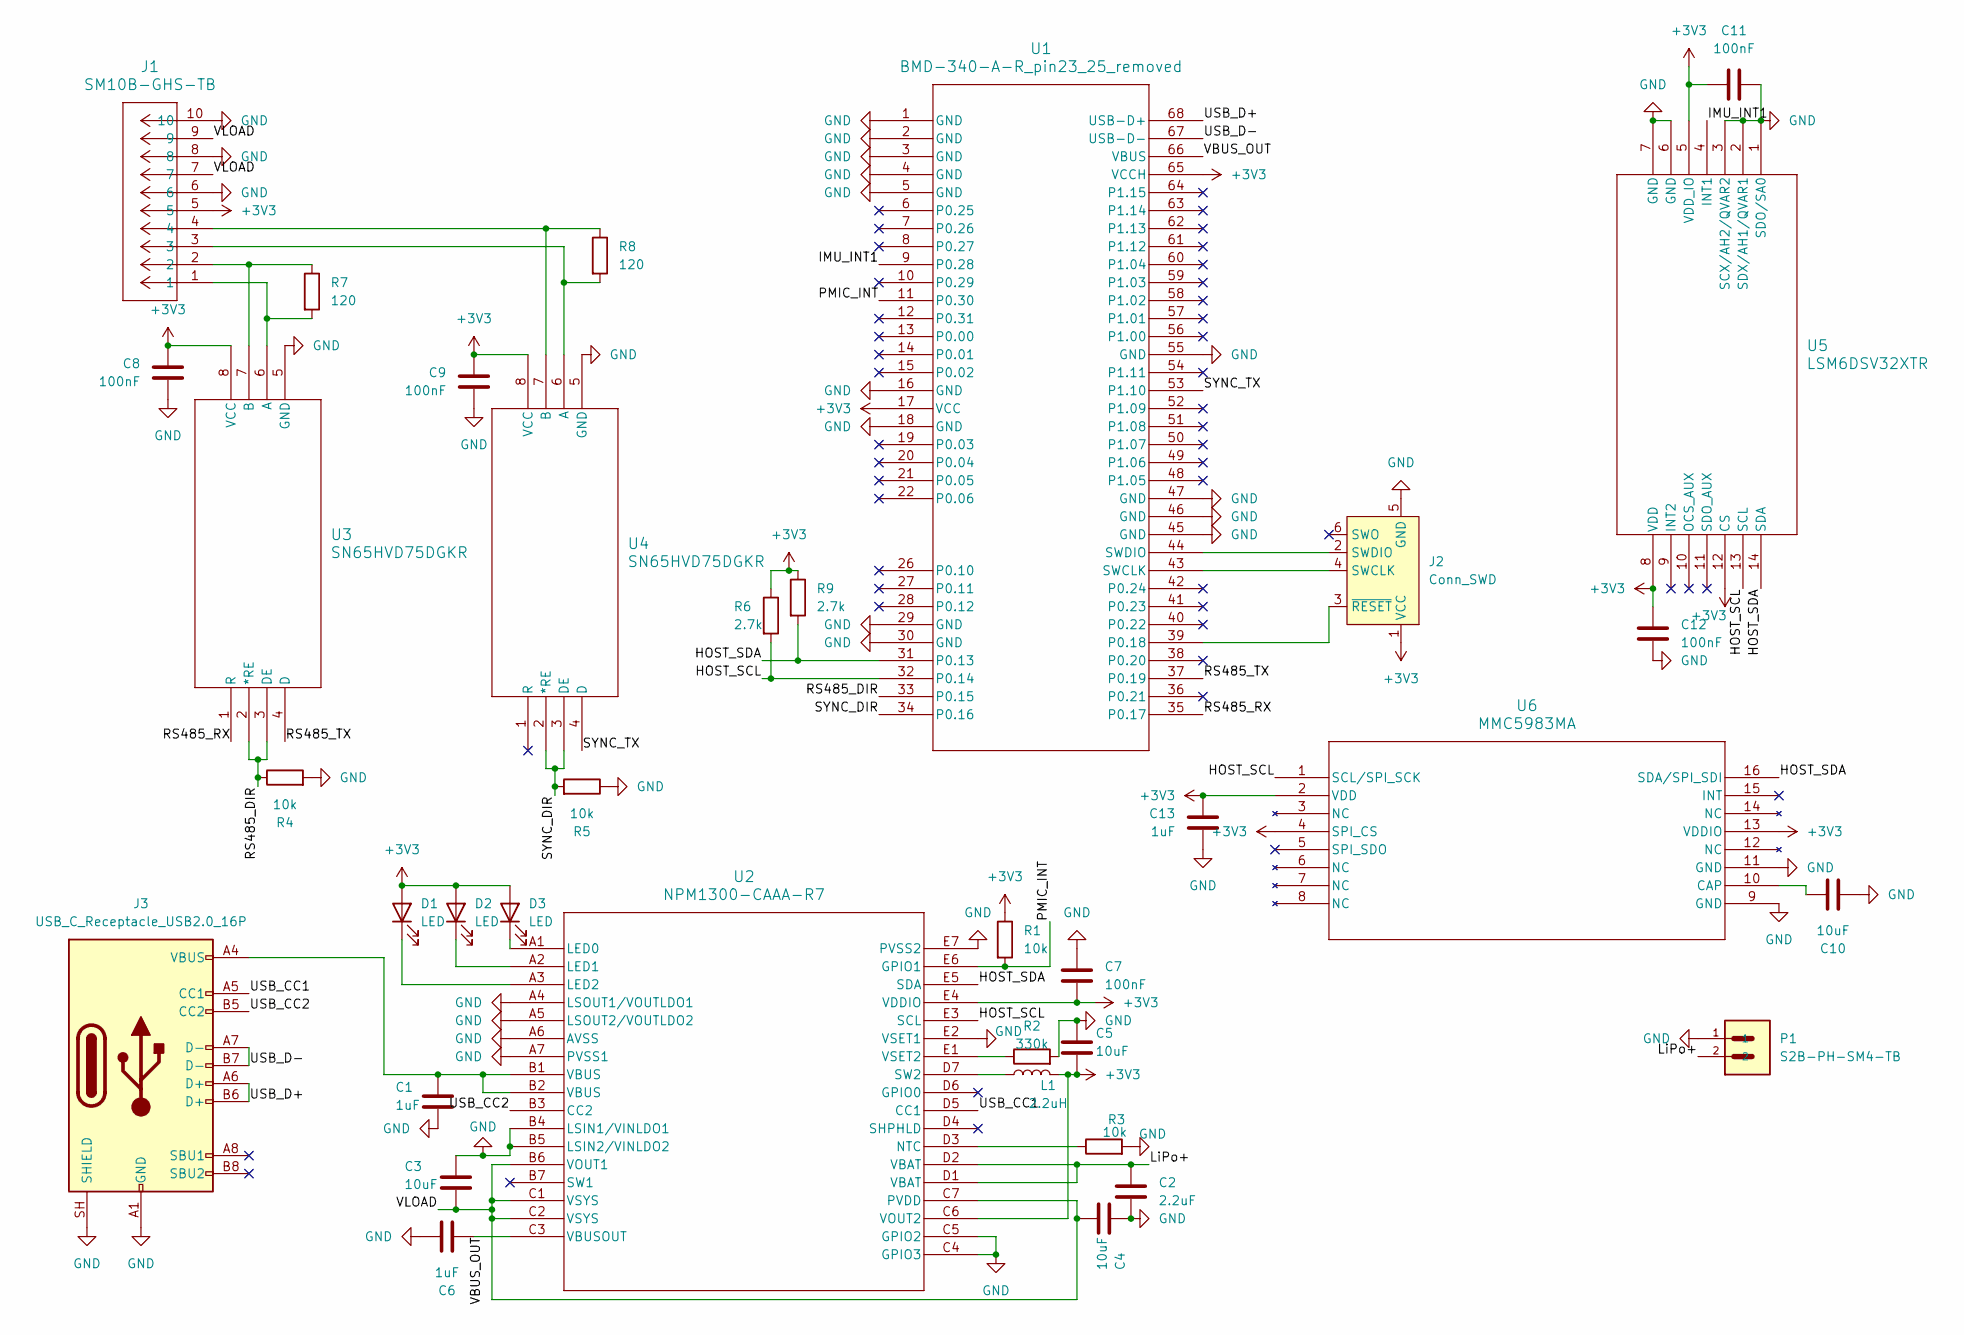
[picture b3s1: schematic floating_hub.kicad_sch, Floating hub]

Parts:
C1, C6, C13: 1uF; C_0603_1608Metric
C2: 2.2uF; C_0603_1608Metric
C3, C4, C5, C10: 10uF; C_0603_1608Metric
C7, C8, C9, C11, C12: 100nF; C_0402_1005Metric
D1, D2, D3: LED; LED_0402_1005Metric
J1: SM10B-GHS-TB; JST_GH_SM10B-GHS-TB_1x10-1MP_P1.25mm_Horizontal
J2: Conn_SWD; Tag-Connect_TC2030-IDC-NL_2x03_P1.27mm_Vertical
J3: USB_C_Receptacle_USB2.0_16P; USB_C_Receptacle_GCT_USB4110
L1: 2.2uH; L_0805_2012Metric
P1: S2B-PH-SM4-TB; JST_PH_S2B-PH-SM4-TB_1x02-1MP_P2.00mm_Horizontal
R1, R3, R4, R5: 10k; R_0402_1005Metric
R2: 330k; R_0402_1005Metric
R6, R9: 2.7k; R_0402_1005Metric
R7, R8: 120; R_0402_1005Metric
U1: BMD-340-A-R_pin23_25_removed; BMD-340_UBL_ncs_removed
U2: NPM1300-CAAA-R7; WLCSP35_2p3775X3p0775_NOR
U3, U4: SN65HVD75DGKR; DGK8_TEX
U5: LSM6DSV32XTR; LGA-14_3x2.5mm_P0.5mm_LayoutBorder3x4y
U6: MMC5983MA; LGA-16_3x3mm_P0.5mm

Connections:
+3V3: C5.2, C7.2, C8.2, C9.2, C11.1, C12.1, C13.2, D1.2 (A), D2.2 (A), D3.2 (A), J1.5, J2.1 (VCC), L1.2, R1.1, R6.1, R9.1, U1.17 (VCC), U1.65 (VCCH), U2.C6 (VOUT2), U2.E4 (VDDIO), U3.8 (VCC), U4.8 (VCC), U5.5 (VDD_IO), U5.8 (VDD), U5.12 (CS), U6.2 (VDD), U6.4 (SPI_CS), U6.13 (VDDIO)
/HOST_SCL: R6.2, U1.32 (P0.14), U2.E3 (SCL), U5.13 (SCL), U6.1 (SCL/SPI_SCK)
/HOST_SDA: R9.2, U1.31 (P0.13), U2.E5 (SDA), U5.14 (SDA), U6.16 (SDA/SPI_SDI)
/IMU_INT1: U1.9 (P0.28), U5.4 (INT1)
/LiPo+: C2.1, P1.2, U2.D1 (VBAT), U2.D2 (VBAT)
/PMIC_INT: R1.2, U1.11 (P0.30), U2.E6 (GPIO1)
/RS485_DIR: R4.1, U1.33 (P0.15), U3.2 (*RE), U3.3 (DE)
/RS485_RX: U1.35 (P0.17), U3.1 (R)
/RS485_TX: U1.37 (P0.19), U3.4 (D)
/SYNC_DIR: R5.2, U1.34 (P0.16), U4.2 (*RE), U4.3 (DE)
/SYNC_TX: U1.53 (P1.10), U4.4 (D)
/USB_CC1: J3.A5 (CC1), U2.D5 (CC1)
/USB_CC2: J3.B5 (CC2), U2.B3 (CC2)
/USB_D+: J3.A6 (D+), J3.B6 (D+), U1.68 (USB-D+)
/USB_D-: J3.A7 (D-), J3.B7 (D-), U1.67 (USB-D-)
/VBUS_OUT: C6.1, U1.66 (VBUS), U2.C3 (VBUSOUT)
/VLOAD: C3.2, C4.2, J1.7, J1.9, U2.B6 (VOUT1), U2.C1 (VSYS), U2.C2 (VSYS), U2.C7 (PVDD)
GND: C1.2, C2.2, C3.1, C4.1, C5.1, C6.2, C7.1, C8.1, C9.1, C10.2, C11.2, C12.2, C13.1, J1.6, J1.8, J1.10, J2.5 (GND), J3.A1 (GND), J3.A12 (GND), J3.B1 (GND), J3.B12 (GND), J3.SH (SHIELD), P1.1, R2.2, R3.2, R4.2, R5.1, U1.1 (GND), U1.2 (GND), U1.3 (GND), U1.4 (GND), U1.5 (GND), U1.16 (GND), U1.18 (GND), U1.29 (GND), U1.30 (GND), U1.45 (GND), U1.46 (GND), U1.47 (GND), U1.55 (GND), U2.A4 (LSOUT1/VOUTLDO1), U2.A5 (LSOUT2/VOUTLDO2), U2.A6 (AVSS), U2.A7 (PVSS1), U2.B4 (LSIN1/VINLDO1), U2.B5 (LSIN2/VINLDO2), U2.C4 (GPIO3), U2.C5 (GPIO2), U2.E2 (VSET1), U2.E7 (PVSS2), U3.5 (GND), U4.5 (GND), U5.1 (SDO/SA0), U5.2 (SDX/AH1/QVAR1), U5.3 (SCX/AH2/QVAR2), U5.6 (GND), U5.7 (GND), U6.9 (GND), U6.11 (GND)
unnamed: C1.1, J3.A4 (VBUS), J3.A9 (VBUS), J3.B4 (VBUS), J3.B9 (VBUS), U2.B1 (VBUS), U2.B2 (VBUS)
unnamed: D1.1 (K), U2.A3 (LED2)
unnamed: D2.1 (K), U2.A2 (LED1)
unnamed: D3.1 (K), U2.A1 (LED0)
unnamed: J2.4 (SWCLK), U1.43 (SWCLK)
unnamed: J2.2 (SWDIO), U1.44 (SWDIO)
unnamed: J2.3 (~RESET), U1.39 (P0.18)
unnamed: R3.1, U2.D3 (NTC)
unnamed: L1.1, U2.D7 (SW2)
unnamed: R2.1, U2.E1 (VSET2)
unnamed: J1.1, R7.2, U3.6 (A)
unnamed: J1.2, R7.1, U3.7 (B)
unnamed: J1.3, R8.2, U4.6 (A)
unnamed: J1.4, R8.1, U4.7 (B)
unnamed: C10.1, U6.10 (CAP)

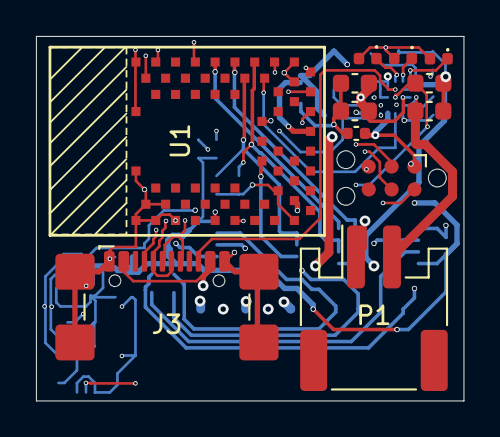
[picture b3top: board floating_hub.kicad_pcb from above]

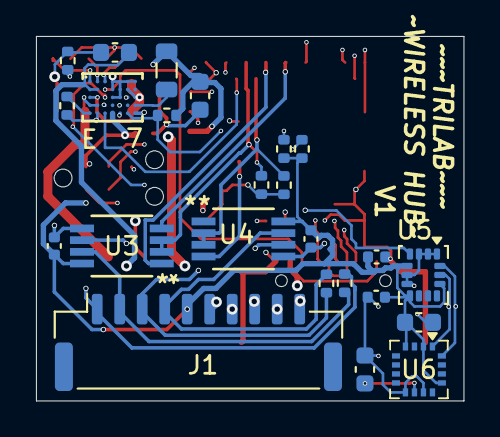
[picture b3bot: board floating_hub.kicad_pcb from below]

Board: 4 copper layers, 23.8 x 20.2 mm, 36 parts (24 on the bottom side), 33 nets.

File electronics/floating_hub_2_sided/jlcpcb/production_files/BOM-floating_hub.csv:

Comment,Designator,Footprint,LCSC,Quantity
100nF,"C11,C12,C7,C8,C9",C_0402_1005Metric,C307331,5
10k,"R1,R3,R4,R5",R_0402_1005Metric,C25744,4
10uF,"C10,C3,C4,C5",C_0603_1608Metric,C96446,4
120,"R7,R8",R_0402_1005Metric,C25079,2
1uF,"C1,C13,C6",C_0603_1608Metric,C15849,3
2.2uF,C2,C_0603_1608Metric,C23630,1
2.2uH,L1,L_0805_2012Metric,C1043,1
2.7k,"R6,R9",R_0402_1005Metric,C25885,2
330k,R2,R_0402_1005Metric,C25778,1
BMD-340-A-R_pin23_25_removed,U1,BMD-340_UBL_ncs_removed,C5456944,1
LED,D3,LED_0402_1005Metric,C22355736,1
LED,D1,LED_0402_1005Metric,C434445,1
LED,D2,LED_0402_1005Metric,C51933302,1
LSM6DSV32XTR,U5,LGA-14_3x2.5mm_P0.5mm_LayoutBorder3x4y,C22461202,1
MMC5983MA,U6,LGA-16_3x3mm_P0.5mm,C404329,1
NPM1300-CAAA-R7,U2,WLCSP35_2p3775X3p0775_NOR,C25346894,1
S2B-PH-SM4-TB,P1,JST_PH_S2B-PH-SM4-TB_1x02-1MP_P2.00mm_Horizontal,C295747,1
SM10B-GHS-TB,J1,JST_GH_SM10B-GHS-TB_1x10-1MP_P1.25mm_Horizontal,C2683602,1
SN65HVD75DGKR,"U3,U4",DGK8_TEX,C179693,2
USB_C_Receptacle_USB2.0_16P,J3,USB_C_Receptacle_GCT_USB4110,C5143397,1

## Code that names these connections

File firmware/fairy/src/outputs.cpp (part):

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
/*
 * Output ownership for the reward-port PCB (STM32G071):
 *   RGB red   PB4 / TIM3_CH1
 *   RGB green PB5 / TIM3_CH2
 *   RGB blue  PB0 / TIM3_CH3
 *   Valve     PA8 / TIM1_CH1 -> DRV8837 IN1 (IN2 is tied to GND)
 *   Audio     PA4 / DAC1_OUT1
 *   Amp enable/shutdown and IR enable remain board-profile/light-sensor owned.
 */

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void initialize_rgb() {
  /*
   * Final PCB and Nucleo prototype use the same RGB timer mapping:
   *   PB4 = TIM3_CH1 (red)
   *   PB5 = TIM3_CH2 (green)
   *   PB0 = TIM3_CH3 (blue)
   *
   * Drive the pins low as ordinary GPIOs first. Only hand them to TIM3 after
   * all compare registers are known to be zero, preventing a startup flash.
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void configure_valve_gpio_safe() {
  __HAL_RCC_GPIOA_CLK_ENABLE();

  /* DRV8837 IN2 is hard-wired low; PA8/TIM1_CH1 is the sole drive input. */
  HAL_GPIO_WritePin(GPIOA, GPIO_PIN_8, GPIO_PIN_RESET);
  GPIO_InitTypeDef gpio{};
  gpio.Pin = GPIO_PIN_8;
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}

void initialize_audio() {
  /* PA4 is DAC1_OUT1. The amplifier remains disabled through board_profile. */
  configure_audio_gpio();
  __HAL_RCC_DAC1_CLK_ENABLE();
  __HAL_RCC_DMA1_CLK_ENABLE();
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  events.clear();

  fairy_debug::log(
      "OUTPUTS_READY rgb=PB4/PB5/PB0@2kHz valve=PA8@25kHz audio=PA4\r\n");
}

void service(std::uint64_t now_ticks) {
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  set_rgb(0, 0, 0, 0, now_ticks);
  finish_audio(now_ticks);

  /* DRV8837 IN2 is grounded: safe state is simply PA8/TIM1_CH1 = 0. */
  if (valve_phase != ValvePhase::idle) {
    finish_valve_cycle(now_ticks);
  } else {
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
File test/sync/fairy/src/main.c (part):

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 * Board: nucleo_g071rb
 *
 * RS-485 connections:
 *   PC4 / D1    -> D   (USART1_TX)
 *   PC5 / D0    <- R   (USART1_RX)
 *   PB5 / D4    -> DE and /RE tied together
 *   A/B/GND    <-> Korora RS-485 transceiver A/B/GND
 *
 * Timing connections retained:
 *   PA0 / A0   <- Korora SYNC pulse (TIM2_CH1)
 *   PA1 / A1   <- shared reward/event input (TIM2_CH2)
 *   PA2/PA3    <-> ST-LINK virtual COM port (USART2 debug)
 *
 * The RS-485 protocol is addressed and retry-safe. A POLL response containing
 * a record is removed from the FIFO only when the following POLL acknowledges
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  __HAL_RCC_GPIOC_CLK_ENABLE();

  /*
   * PA0 / TIM2_CH1:
   * RS-485 receiver's normal logic output.
   * Idle is high and the transported sync pulse is active-low.
   */
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  HAL_GPIO_Init(GPIOA, &gpio);

  /*
   * PA1 / TIM2_CH2:
   * Existing local reward/event input, active-high.
   */
  gpio.Pin = GPIO_PIN_1;
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  gpio.Alternate = GPIO_AF1_USART2;
  HAL_GPIO_Init(GPIOA, &gpio);

  /* Arduino D1: PC4 = USART1_TX. */
  gpio.Pin = GPIO_PIN_4;
  gpio.Mode = GPIO_MODE_AF_PP;
  gpio.Pull = GPIO_NOPULL;
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  HAL_GPIO_Init(GPIOC, &gpio);

  /*
   * Arduino D0: PC5 = USART1_RX.
   * Pull up because the THVD1410 R output is high-Z while /RE is high.
   */
  gpio.Pin = GPIO_PIN_5;
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  gpio.Alternate = GPIO_AF1_USART1;
  HAL_GPIO_Init(GPIOC, &gpio);

  /* PB5 drives tied THVD1410 DE and /RE. Default to receive. */
  HAL_GPIO_WritePin(GPIOB, GPIO_PIN_5, GPIO_PIN_RESET);
  gpio.Pin = GPIO_PIN_5;
  gpio.Mode = GPIO_MODE_OUTPUT_PP;
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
